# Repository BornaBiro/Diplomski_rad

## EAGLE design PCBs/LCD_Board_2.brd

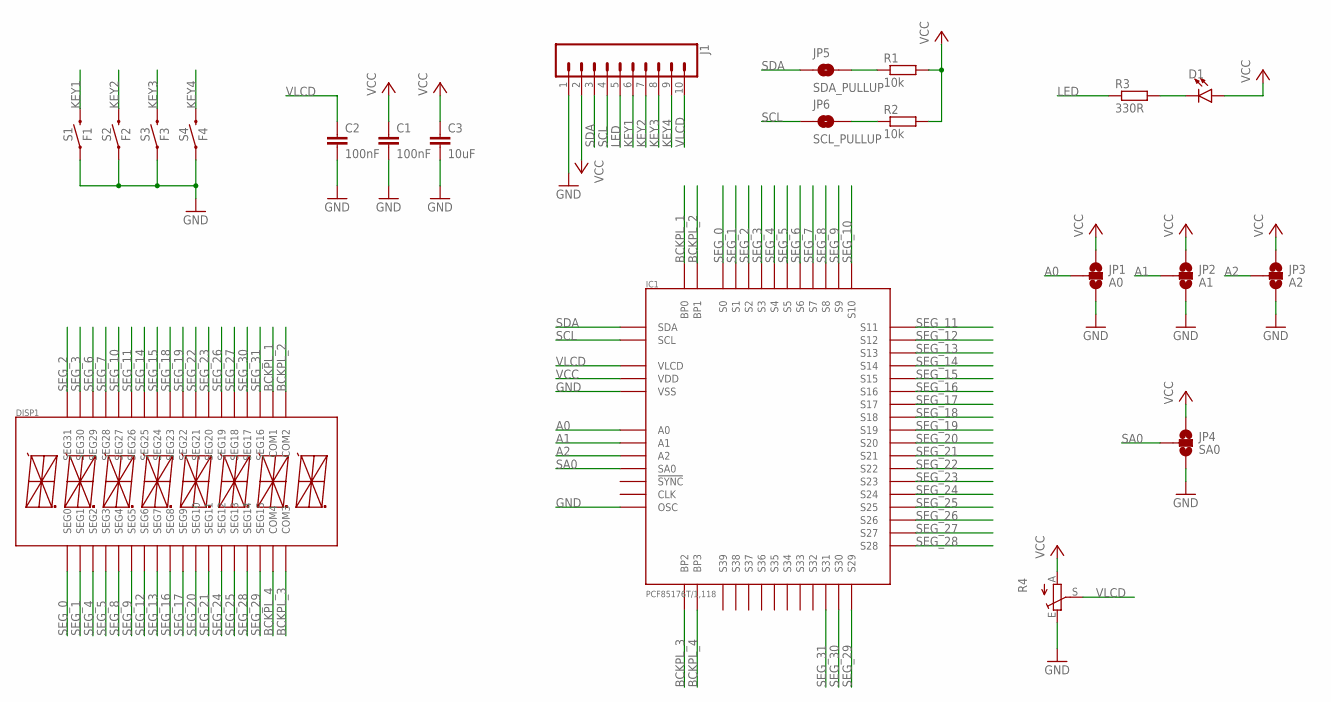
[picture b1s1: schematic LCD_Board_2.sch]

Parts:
C1, C2: 100nF; C0603K
C3: 10uF; C1206K
D1: LED3MM; LED_3MM
DISP1: DE301-RS-20/6.35-3
IC1: PCF85176T/1,118; TSSOP56
J1: CONN_10"; 1X10
JP1: A0; SMT-JUMPER_3_NO_SILK
JP2: A1; SMT-JUMPER_3_NO_SILK
JP3: A2; SMT-JUMPER_3_NO_SILK
JP4: SA0; SMT-JUMPER_3_NO_SILK
JP5: SDA_PULLUP; SMT-JUMPER_2_NO_SILK
JP6: SCL_PULLUP; SMT-JUMPER_2_NO_SILK
R1, R2: 10k; R0603
R3: 330R; R0603
R4: TRIM_EU-CA6V; CA6V
S1: F1; TACTILE_SWITCH_SMD_5.2MM
S2: F2; TACTILE_SWITCH_SMD_5.2MM
S3: F3; TACTILE_SWITCH_SMD_5.2MM
S4: F4; TACTILE_SWITCH_SMD_5.2MM

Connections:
A0: IC1.P$50 (A0), JP1.2
A1: IC1.P$51 (A1), JP2.2
A2: IC1.P$52 (A2), JP3.2
BCKPL_1: DISP1.P$20 (COM1), IC1.P$56 (BP0)
BCKPL_2: DISP1.P$19 (COM2), IC1.P$2 (BP1)
BCKPL_3: DISP1.P$18 (COM3), IC1.P$1 (BP2)
BCKPL_4: DISP1.P$17 (COM4), IC1.P$3 (BP3)
GND: C1.2, C2.2, C3.2, IC1.P$49 (OSC), IC1.P$54 (VSS), J1.1, JP1.3, JP2.3, JP3.3, JP4.3, R4.E, S1.1, S2.1, S3.1, S4.1
KEY1: J1.6, S1.3 (2)
KEY2: J1.7, S2.3 (2)
KEY3: J1.8, S3.3 (2)
KEY4: J1.9, S4.3 (2)
LED: J1.5, R3.1
unnamed: JP5.2, R1.1
unnamed: JP6.2, R2.1
unnamed: D1.K (C), R3.2
SA0: IC1.P$53 (SA0), JP4.2
SCL: IC1.P$45 (SCL), J1.4, JP6.1
SDA: IC1.P$44 (SDA), J1.3, JP5.1
SEG_0: DISP1.P$1 (SEG0), IC1.P$4 (S0)
SEG_1: DISP1.P$2 (SEG1), IC1.P$5 (S1)
SEG_2: DISP1.P$36 (SEG31), IC1.P$6 (S2)
SEG_3: DISP1.P$35 (SEG30), IC1.P$7 (S3)
SEG_4: DISP1.P$3 (SEG2), IC1.P$8 (S4)
SEG_5: DISP1.P$4 (SEG3), IC1.P$9 (S5)
SEG_6: DISP1.P$34 (SEG29), IC1.P$10 (S6)
SEG_7: DISP1.P$33 (SEG28), IC1.P$11 (S7)
SEG_8: DISP1.P$5 (SEG4), IC1.P$12 (S8)
SEG_9: DISP1.P$6 (SEG5), IC1.P$13 (S9)
SEG_10: DISP1.P$32 (SEG27), IC1.P$14 (S10)
SEG_11: DISP1.P$31 (SEG26), IC1.P$15 (S11)
SEG_12: DISP1.P$7 (SEG6), IC1.P$16 (S12)
SEG_13: DISP1.P$8 (SEG7), IC1.P$17 (S13)
SEG_14: DISP1.P$30 (SEG25), IC1.P$18 (S14)
SEG_15: DISP1.P$29 (SEG24), IC1.P$19 (S15)
SEG_16: DISP1.P$9 (SEG8), IC1.P$20 (S16)
SEG_17: DISP1.P$10 (SEG9), IC1.P$21 (S17)
SEG_18: DISP1.P$28 (SEG23), IC1.P$22 (S18)
SEG_19: DISP1.P$27 (SEG22), IC1.P$23 (S19)
SEG_20: DISP1.P$11 (SEG10), IC1.P$24 (S20)
SEG_21: DISP1.P$12 (SEG11), IC1.P$25 (S21)
SEG_22: DISP1.P$26 (SEG21), IC1.P$26 (S22)
SEG_23: DISP1.P$25 (SEG20), IC1.P$27 (S23)
SEG_24: DISP1.P$13 (SEG12), IC1.P$28 (S24)
SEG_25: DISP1.P$14 (SEG13), IC1.P$29 (S25)
SEG_26: DISP1.P$24 (SEG19), IC1.P$30 (S26)
SEG_27: DISP1.P$23 (SEG18), IC1.P$31 (S27)
SEG_28: DISP1.P$15 (SEG14), IC1.P$32 (S28)
SEG_29: DISP1.P$16 (SEG15), IC1.P$33 (S29)
SEG_30: DISP1.P$22 (SEG17), IC1.P$34 (S30)
SEG_31: DISP1.P$21 (SEG16), IC1.P$35 (S31)
VCC: C1.1, C3.1, D1.A, IC1.P$48 (VDD), J1.2, JP1.1, JP2.1, JP3.1, JP4.1, R1.2, R2.2, R4.A
VLCD: C2.1, IC1.P$55 (VLCD), J1.10, R4.S

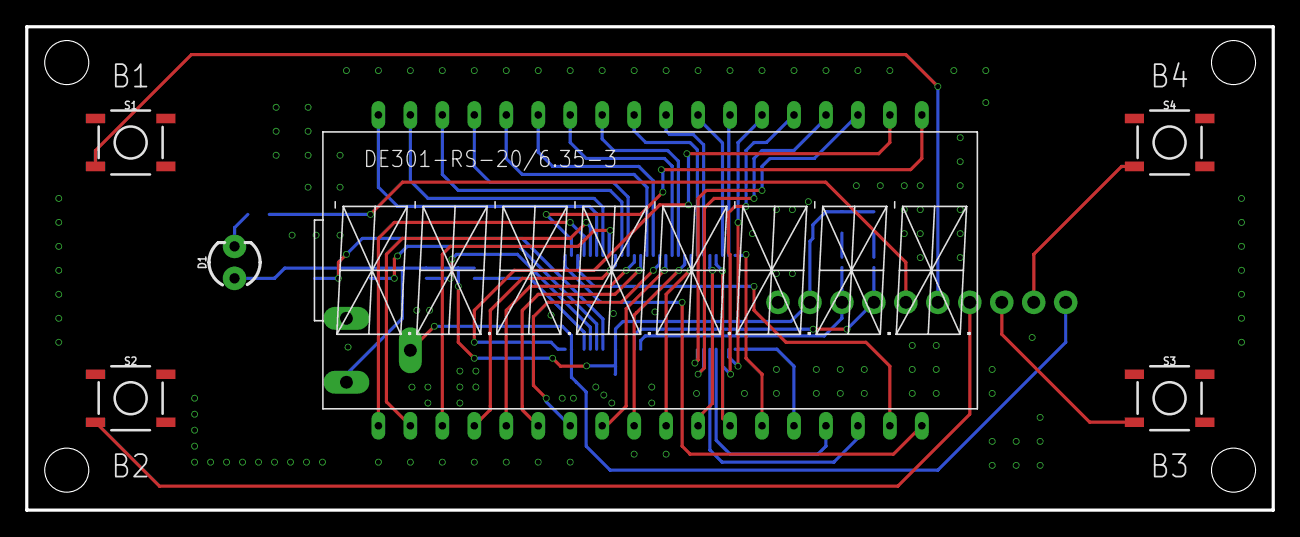
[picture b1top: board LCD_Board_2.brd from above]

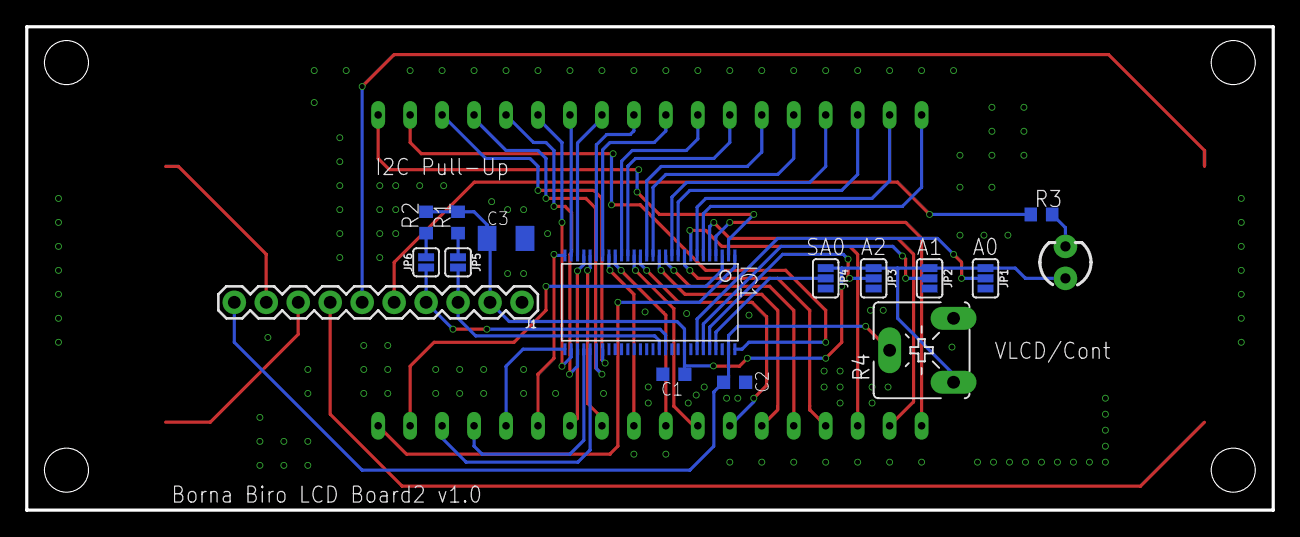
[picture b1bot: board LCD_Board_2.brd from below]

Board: 2 copper layers, 99.0 x 38.4 mm, 21 parts (15 on the bottom side), 53 nets.

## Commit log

2021-05-15 Added LCD files, added RTC Alarm, better RTC functions
2021-05-17 LCD files renamed to glassLCD, written LCD functions, fixed issue with RTC Alarm Interrupt
    NOTE FOR RTC ALARM INTERRUPT:
    Proper function name for RTC Interrupt handler is RTC_IRQHandler() NOT RTC_Alarm_IRQHandler() (that is used for STM32H7XX)!
2021-05-21 Added STM32 Atollic TrueSTUDIO Code for Outdoor unit
    Switching from Arduino (STM32duino) because it's memory inefficient to STM32 Atollic TrueSTUDIO.
2021-05-25 Added sleep library, added BMP180 .c and .h files, fixed code for glassLCD library (dot problem)
2021-07-07 Added .docx file
2021-07-18 Added new keyboard, removed old code for keyboard
2021-07-19 Added uncompleted code for listBox, commented out test codes for keyboard and textbox
2021-07-21 Fully added list box with touchscreen
2021-07-21 Added example for keyboard, textbox, listbox and WiFi
2021-07-26 Added Si1147 driver, but still not finished and tested
2021-07-26 Finished Si1147 driver and added test code to main.c
    To-Do: Add error handler if sensors haven't been found (write some error on LCD).
2021-08-17 Files split into folders, added modified NRF24L01 library for STM32 and Inkplate
2021-08-17 Remover pgm_read_byte from ESP32 RF24 lib, added CSN and CE pins in RF24_init function
2021-09-04 Added check for all sensors, added nRF24l01, added sync between indoor and outdoor unit
2021-09-19 Added second button for instant measurement on PB1 and changed button for changing display on PA8
2021-10-12 Added all Arduino experimental codes, added real nRF indoor unit communication example, added nRF communication on STM32 outdoor unit (and fixed all STM32 RTC errors)
2021-10-24 Added code for STM32L073 (outdoor unit PCB)
2021-10-25 Now all measured data is been transmitted, added functions for sync and sending data, fixed rounding error on LCD, LCD is now being cleared every time new data has been written, fixed compiler warnin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
2021-10-26 Fixed rounding error on solar data
2021-10-28 Fixed UV readings bug, added abs() on some display values
2021-10-29 Added wind speed scaling
2021-11-29 Added 3D models, PCBs, split into folders
2022-10-29 Added limit to the humidity, solar cell current change
    Added limit to the humidity (for some reason SHT21 could read more than 100.0% (ex. 100.5%).
    If 100% of RH is measured, remove dot for RH on LCD.
    Solar cell is 40mA, not 45mA.
2022-10-31 Added wind speed scaling, longer timeout for wind speed reading.
2022-10-31 Added wind speed holder bar.
2022-11-06 Fixed humidity on LCD, fixed wind speed calculations
    There was a bug when humidity was around 99.55% (LCD will show 10.0%, because of the rounding).
    New calculation on wind speed (linear regression instead of power regression).

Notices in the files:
parts and their libraries:
SparkFun-Switches: Licensing: Creative Commons ShareAlike 4.0 International - https://creativecommons.org/licenses/by-sa/4.0
